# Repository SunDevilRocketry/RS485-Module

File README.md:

# RS485-Module
Prototype Board for an RS485 Transceiver interface

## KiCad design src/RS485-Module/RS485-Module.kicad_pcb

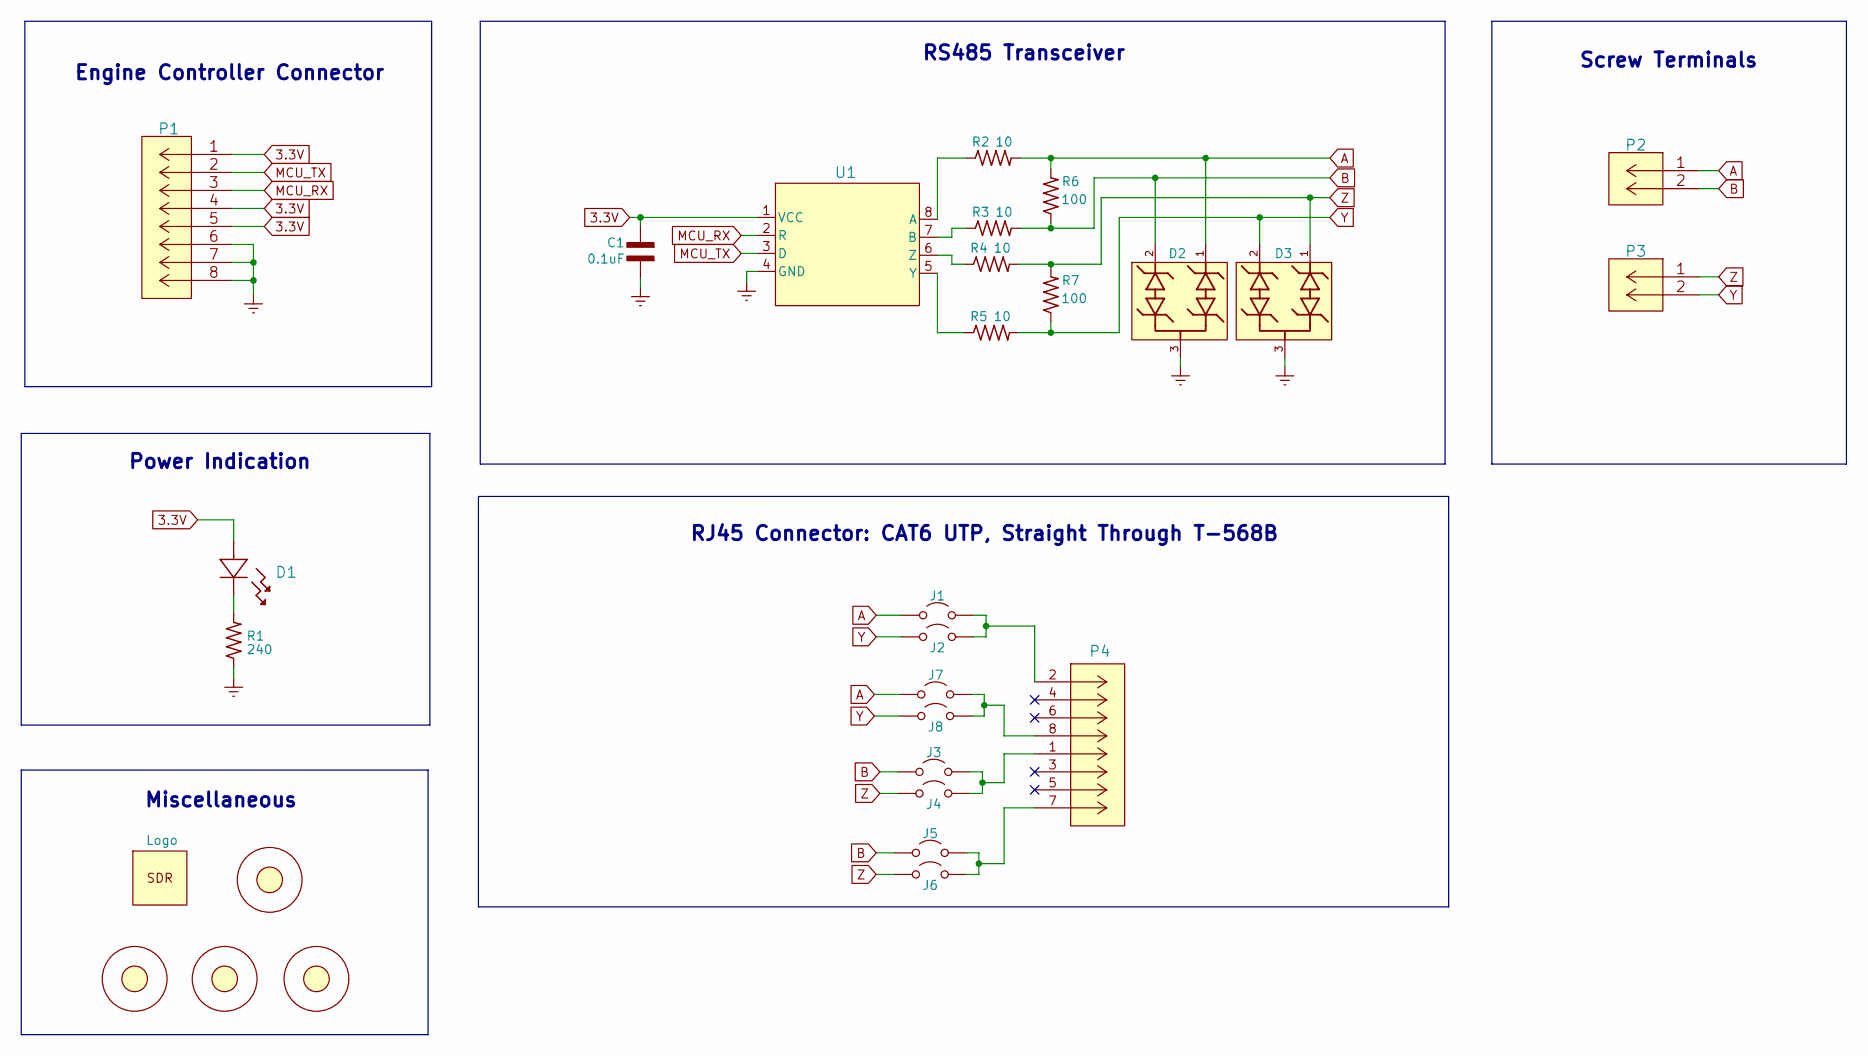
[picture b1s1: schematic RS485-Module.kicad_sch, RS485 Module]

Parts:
C1: 0.1uF; CAP_0603
D1: SML-LX1206GC-TR
D2, D3: SMBJ36CA-13-F; CDSOT23-SM712; PARTREV 20-2
H1, H2, H3, H4: Mounting-Hole; MountingHole_4.3mm_M4_DIN965
J1, J2, J3, J4, J5, J6, J7, J8: Jumper_NO; Jumper-NO
LOGO1: Logo
P1: 5015680807
P2, P3: 282837-2
P4: 54602-908LF
R1: 240; RES_0603
R2, R3, R4, R5: 10; RES_0603
R6, R7: 100; RES_0603
U1: SN65HVD71DR

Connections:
3.3V: C1.1, D1.2, P1.1, P1.4, P1.5, U1.1 (VCC)
A: D2.1, J1.1 (A), J7.1 (A), P2.1 (5), R2.2, R6.2
B: D2.2, J3.1 (A), J5.1 (A), P2.2 (6), R3.2, R6.1
Earth: C1.2, D2.3, D3.3, P1.6, P1.7, P1.8, R1.1, U1.4 (GND)
MCU_RX: P1.3, U1.2 (R)
MCU_TX: P1.2, U1.3 (D)
unnamed: D1.1, R1.2
unnamed: J1.2 (B), J2.2 (B), P4.2
unnamed: J3.2 (B), J4.2 (B), P4.1
unnamed: J5.2 (B), J6.2 (B), P4.7
unnamed: J7.2 (B), J8.2 (B), P4.8
unnamed: R2.1, U1.8 (A)
unnamed: R3.1, U1.7 (B)
unnamed: R5.1, U1.5 (Y)
unnamed: R4.1, U1.6 (Z)
Y: D3.2, J2.1 (A), J8.1 (A), P3.2 (6), R5.2, R7.1
Z: D3.1, J4.1 (A), J6.1 (A), P3.1 (5), R4.2, R7.2

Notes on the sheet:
Screw Terminals
Miscellaneous
RJ45 Connector: CAT6 UTP, Straight Through T-568B
Engine Controller Connector
Power Indication
RS485 Transceiver

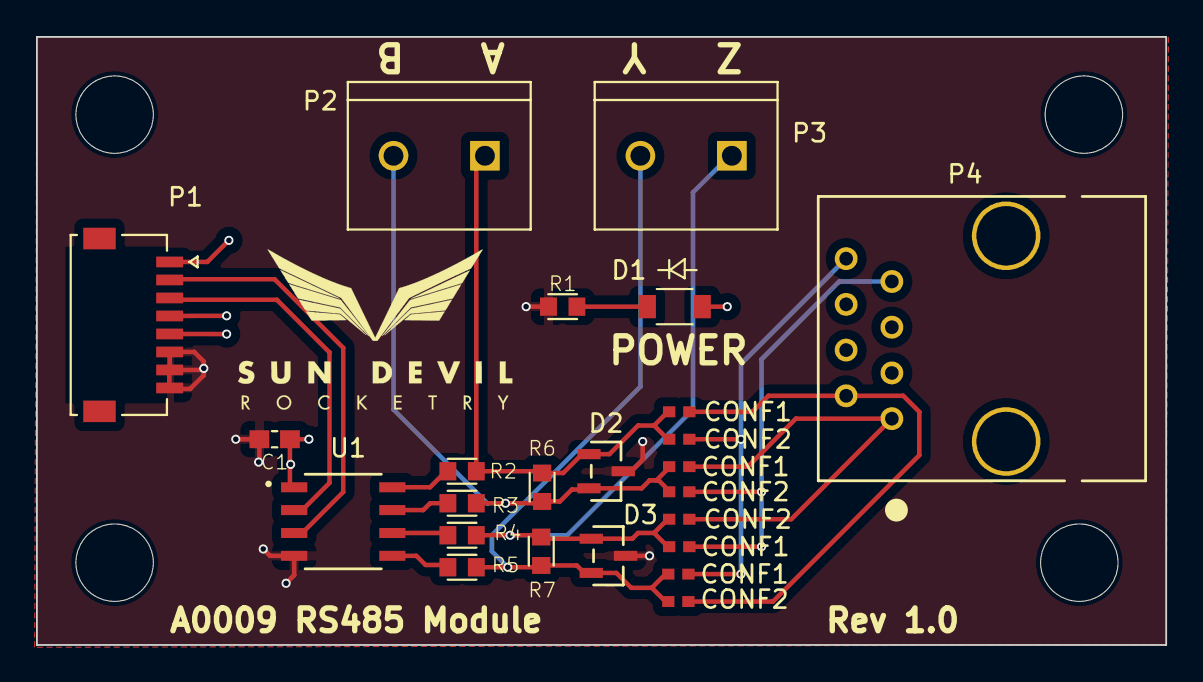
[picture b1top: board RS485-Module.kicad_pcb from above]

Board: 4 copper layers, 62.7 x 33.8 mm, 29 parts (0 on the bottom side), 17 nets.

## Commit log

2023-04-08 created working directory structure
2023-04-08 created kicad project
2023-04-08 created lib files
2023-04-09 completed lib files
2023-04-09 implemented schematic
2023-04-09 placed components in layoyut
2023-04-09 finished rev 1 routing
2023-04-09 generated fabrication outputs

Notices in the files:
parts and their libraries:
Copyright 2021 Accelerated Designs. All rights reserved.
